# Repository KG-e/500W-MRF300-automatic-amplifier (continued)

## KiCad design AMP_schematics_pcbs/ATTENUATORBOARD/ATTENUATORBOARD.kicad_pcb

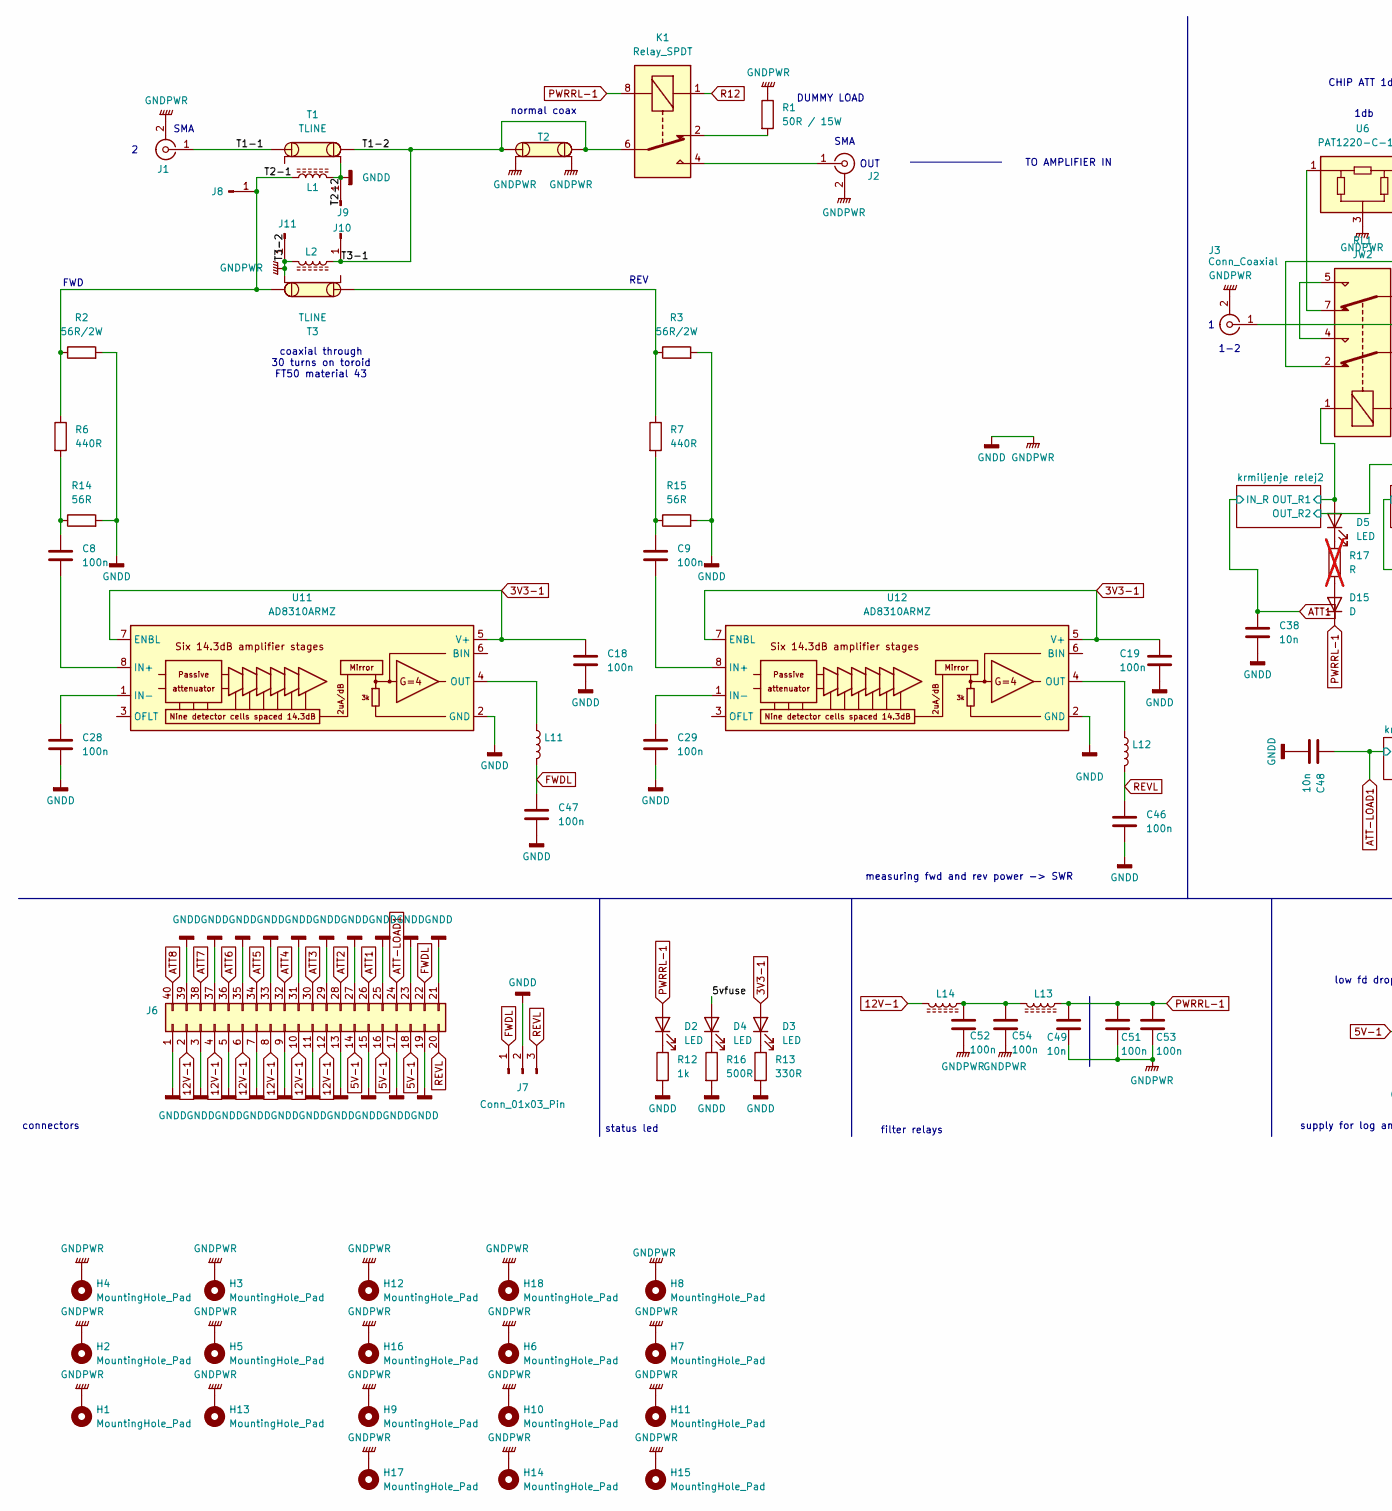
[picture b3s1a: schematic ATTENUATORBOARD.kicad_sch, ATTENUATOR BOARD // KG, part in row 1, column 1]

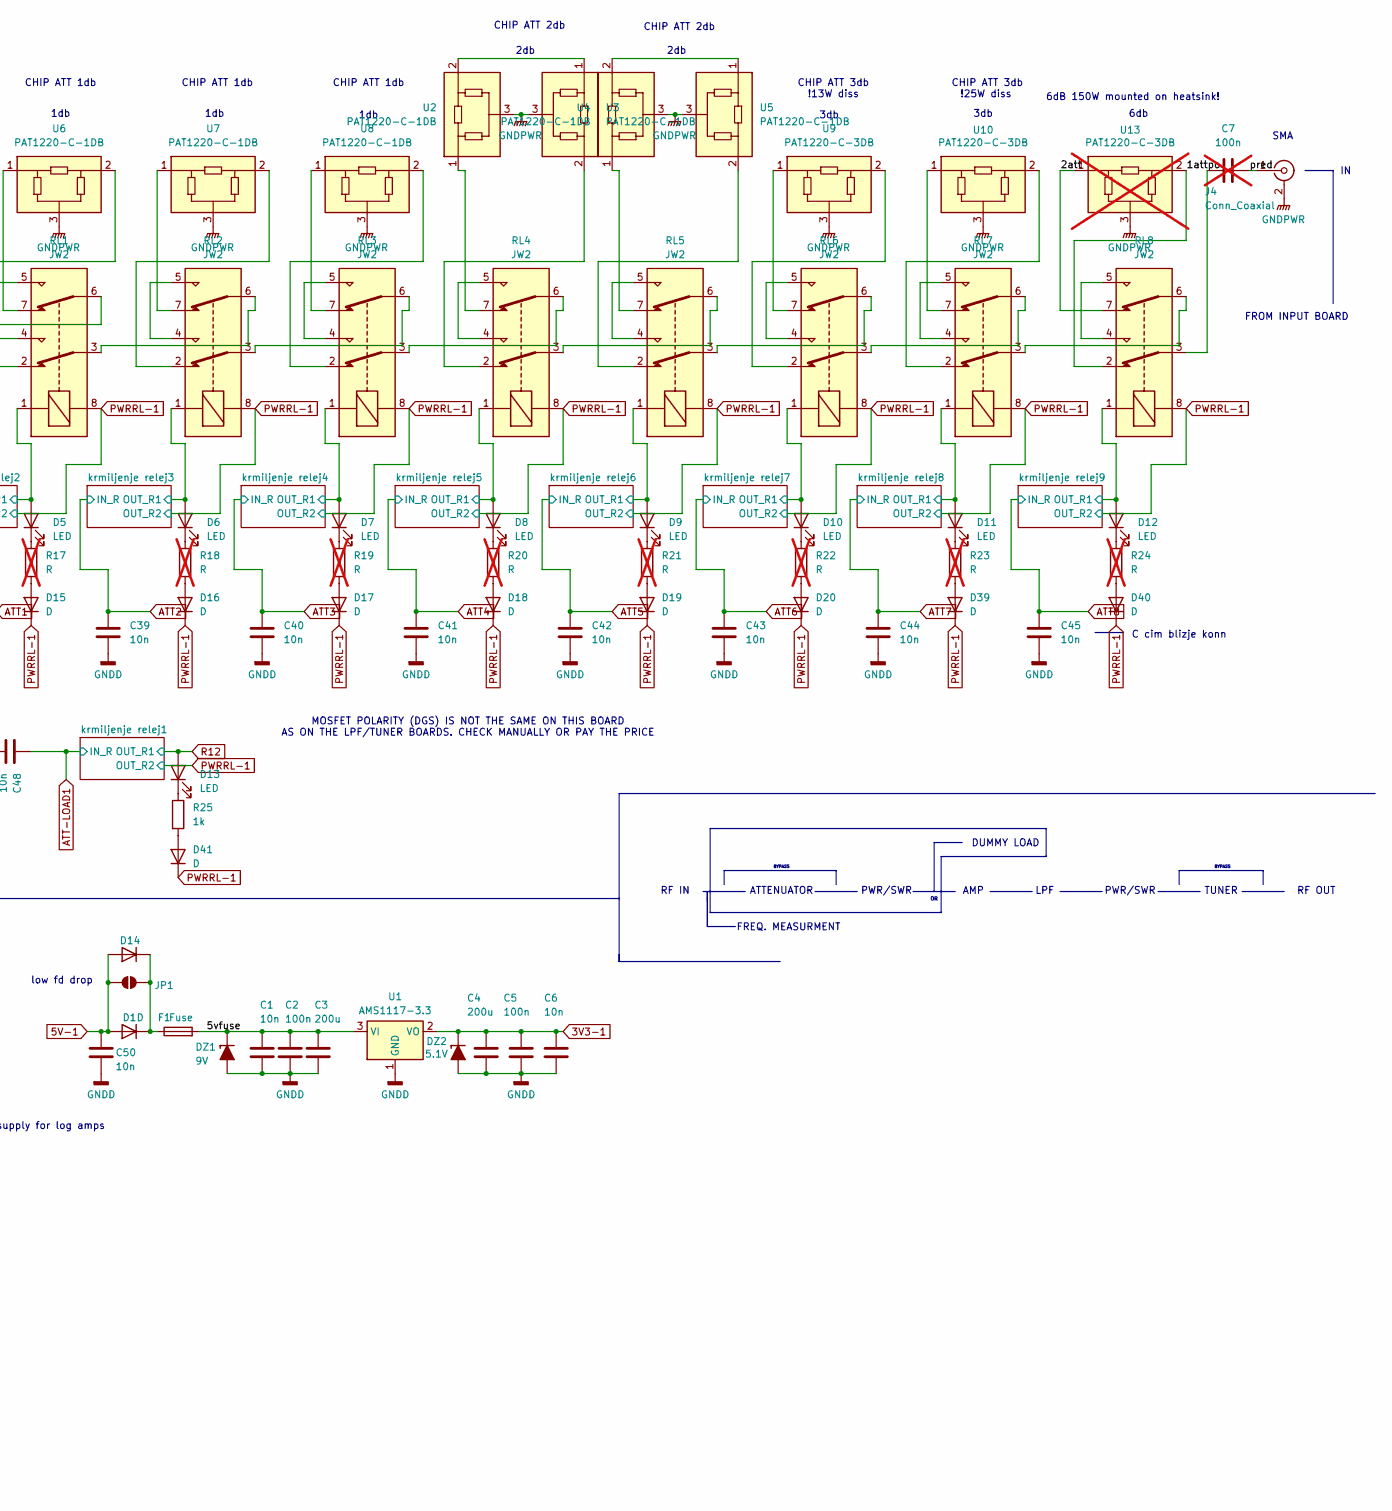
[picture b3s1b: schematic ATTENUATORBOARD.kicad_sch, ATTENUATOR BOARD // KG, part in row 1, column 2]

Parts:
C1, C6, C38, C39, C40, C41, C42, C43, C44, C45, C48, C49, C50: 10n; C_1206_3216Metric_Pad1.33x1.80mm_HandSolder
C2, C5, C8, C9, C18, C19, C28, C29, C46, C47, C51, C52, C53, C54: 100n; C_1206_3216Metric_Pad1.33x1.80mm_HandSolder
C3, C4: 200u; CP_Elec_8x10
C7: 100n; not fitted
D1: D; D_P600_R-6_P12.70mm_Horizontal
D2, D3, D4, D5, D6, D7, D8, D9, D10, D11, D12, D13: LED; LED_0805_2012Metric_Pad1.15x1.40mm_HandSolder
D14, D15, D16, D17, D18, D19, D20, D39, D40, D41: D; D_1206_3216Metric_Pad1.42x1.75mm_HandSolder
DZ1: 9V; D_SOD-123_Zener
DZ2: 5.1V; D_SOD-123_Zener
F1: Fuse; Fuse_1206_3216Metric
H1, H2, H3, H4, H5, H13: MountingHole_Pad; MountingHole_4.3mm_M4_Pad_TopBottom
H6, H7, H8, H9, H10, H11, H12, H14, H15, H16, H17, H18: MountingHole_Pad; MountingHole_3.2mm_M3_Pad_TopBottom
J1, J2, J3, J4: Conn_Coaxial; SMA_Amphenol_132134_Vertical
J6: Conn_02x20_Counter_Clockwise; PinHeader_2x20_P2.54mm_Vertical
J7: Conn_01x03_Pin; PinHeader_1x03_P2.54mm_Vertical
J8, J9, J10, J11: Conn_01x01_Pin; PinSocket_1x01_P2.54mm_Vertical
JP1: SolderJumper_2_Open; SolderJumper-2_P1.3mm_Open_Pad1.0x1.5mm
K1: Relay_SPDT; Relay_SPDT_Panasonic_JW1_FormC
L1, L2: L_Ferrite
L11, L12: L; Ferrite_1206_3216Metric_Pad1.42x1.75mm_BigPads
L13, L14: L_Ferrite; Ferrite_1206_3216Metric_Pad1.22x1.90mm_BigPads
R1: 50R / 15W; TO-220-2_Horizontal_TabDown
R2, R3: 56R/2W; R_2512_6332Metric_Pad1.40x3.35mm_HandSolder
R6, R7: 440R; R_1206_3216Metric_Pad1.30x1.75mm_HandSolder
R12, R25: 1k; R_1206_3216Metric_Pad1.30x1.75mm_HandSolder
R13: 330R; R_1206_3216Metric_Pad1.30x1.75mm_HandSolder
R14, R15: 56R; R_1206_3216Metric_Pad1.30x1.75mm_HandSolder
R16: 500R; R_1206_3216Metric_Pad1.30x1.75mm_HandSolder
R17, R18, R19, R20, R21, R22, R23, R24: R; R_1206_3216Metric_Pad1.30x1.75mm_HandSolder; not fitted
RL1, RL2, RL3, RL4, RL5, RL6, RL7, RL8: JW2; Relay_DPDT_Panasonic_JW2
T1, T2, T3: TLINE
U1: AMS1117-3.3; SOT-223-3_TabPin2
U2, U3, U4, U5, U6, U7, U8: PAT1220-C-1DB; ATT-CHIP
U9, U10: PAT1220-C-3DB; ATT-CHIP
U11, U12: AD8310ARMZ; MSOP-8_3x3mm_P0.65mm
U13: PAT1220-C-3DB; ATT-CHIP; not fitted

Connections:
3V3-1: C4.1, C5.1, C6.1, C18.1, C19.1, D3.2 (A), DZ2.1 (K), U1.2 (VO), U11.5 (V+), U11.7 (ENBL), U12.5 (V+), U12.7 (ENBL)
5V-1: C50.1, D1.2 (A), D14.2 (A), J6.14, J6.16, J6.18, JP1.1 (A)
12V-1: J6.2, J6.4, J6.6, J6.8, J6.10, J6.12, L14.2
/1att: RL8.2, U13.2
/2att: RL8.7, U13.1
/5vfuse: C1.1, C2.1, C3.1, D4.2 (A), DZ1.1 (K), F1.2, U1.3 (VI)
/T1-1: J1.1 (In), T1.1
/T1-2: J10.1, K1.6, L2.1, T1.3, T2.1, T2.3
/T2-1: J8.1, L1.1, R2.1, R6.1, T3.3
/krmiljenje relej2/OUT_R1: D5.2 (A), RL1.1; also elsewhere on the board
/krmiljenje relej3/OUT_R1: D6.2 (A), RL2.1; also elsewhere on the board
/krmiljenje relej4/OUT_R1: D7.2 (A), RL3.1; also elsewhere on the board
/krmiljenje relej5/OUT_R1: D8.2 (A), RL4.1; also elsewhere on the board
/krmiljenje relej6/OUT_R1: D9.2 (A), RL5.1; also elsewhere on the board
/krmiljenje relej7/OUT_R1: D10.2 (A), RL6.1; also elsewhere on the board
/krmiljenje relej8/OUT_R1: D11.2 (A), RL7.1; also elsewhere on the board
/krmiljenje relej9/OUT_R1: D12.2 (A), RL8.1; also elsewhere on the board
/po: C7.1, RL8.3
/pred: C7.2, J4.1 (In)
ATT1: C38.1, J6.26; also elsewhere on the board
ATT2: C39.1, J6.28; also elsewhere on the board
ATT3: C40.1, J6.30; also elsewhere on the board
ATT4: C41.1, J6.32; also elsewhere on the board
ATT5: C42.1, J6.34; also elsewhere on the board
ATT6: C43.1, J6.36; also elsewhere on the board
ATT7: C44.1, J6.38; also elsewhere on the board
ATT8: C45.1, J6.40; also elsewhere on the board
ATT-LOAD1: C48.1, J6.24; also elsewhere on the board
FWDL: C47.1, J6.22, J7.1, L11.2
GNDD: C1.2, C2.2, C3.2, C4.2, C5.2, C6.2, C18.2, C19.2, C28.2, C29.2, C38.2, C39.2, C40.2, C41.2, C42.2, C43.2, C44.2, C45.2, C46.2, C47.2, C48.2, C49.2, C50.2, C51.2, C52.2, C53.2, C54.2, DZ1.2 (A), DZ2.2 (A), H1.1, H2.1, H3.1, H4.1, H5.1, H6.1, H7.1, H8.1, H9.1, H10.1, H11.1, H12.1, H13.1, H14.1, H15.1, H16.1, H17.1, H18.1, J1.2 (Ext), J2.2 (Ext), J3.2 (Ext), J4.2 (Ext), J6.1, J6.3, J6.5, J6.7, J6.9, J6.11, J6.13, J6.15, J6.17, J6.19, J6.21, J6.23, J6.25, J6.27, J6.29, J6.31, J6.33, J6.35, J6.37, J6.39, J7.2, J9.1, J11.1, L1.2, L2.2, R1.1, R2.2, R3.2, R12.2, R13.2, R14.2, R15.2, R16.2, T1.4, T2.2, T2.4, T3.4, U1.1 (GND), U2.3, U3.3, U4.3, U5.3, U6.3, U7.3, U8.3, U9.3, U10.3, U11.2 (GND), U12.2 (GND), U13.3; also elsewhere on the board
unnamed: C8.1, R6.2, R14.1
unnamed: C9.1, R7.2, R15.1
unnamed: C52.1, C54.1, L13.2, L14.1
unnamed: D1.1 (K), D14.1 (K), F1.1, JP1.2 (B)
unnamed: D2.1 (K), R12.1
unnamed: D3.1 (K), R13.1
unnamed: D4.1 (K), R16.1
unnamed: D5.1 (K), R17.1
unnamed: D6.1 (K), R18.1
unnamed: D7.1 (K), R19.1
unnamed: D8.1 (K), R20.1
unnamed: D9.1 (K), R21.1
unnamed: D10.1 (K), R22.1
unnamed: D11.1 (K), R23.1
unnamed: D12.1 (K), R24.1
unnamed: D13.1 (K), R25.1
unnamed: D15.2 (A), R17.2
unnamed: D16.2 (A), R18.2
unnamed: D17.2 (A), R19.2
unnamed: D18.2 (A), R20.2
unnamed: D19.2 (A), R21.2
unnamed: D20.2 (A), R22.2
unnamed: D39.2 (A), R23.2
unnamed: D40.2 (A), R24.2
unnamed: D41.2 (A), R25.2
unnamed: J2.1 (In), K1.4
unnamed: J3.1 (In), RL1.6
unnamed: K1.2, R1.2
unnamed: R3.1, R7.1, T3.1
unnamed: RL1.2, U6.2
unnamed: RL1.3, RL2.6
unnamed: RL1.4, RL1.5
unnamed: RL1.7, U6.1
unnamed: RL2.2, U7.2
unnamed: RL2.3, RL3.6
unnamed: RL2.4, RL2.5
unnamed: RL2.7, U7.1
unnamed: RL3.2, U8.2
unnamed: RL3.3, RL4.6
unnamed: RL3.4, RL3.5
unnamed: RL3.7, U8.1
unnamed: RL4.2, U3.2
unnamed: RL4.3, RL5.6
unnamed: RL4.4, RL4.5
unnamed: RL4.7, U2.1
unnamed: RL5.2, U5.2
unnamed: RL5.3, RL6.6
unnamed: RL5.4, RL5.5
unnamed: RL5.7, U4.1
unnamed: RL6.2, U9.2
unnamed: RL6.3, RL7.6
unnamed: RL6.4, RL6.5
unnamed: RL6.7, U9.1
unnamed: RL7.2, U10.2
unnamed: RL7.3, RL8.6
unnamed: RL7.4, RL7.5
unnamed: RL7.7, U10.1
unnamed: RL8.4, RL8.5
unnamed: U2.2, U3.1
unnamed: U4.2, U5.1
unnamed: C8.2, U11.8 (IN+)
unnamed: C28.1, U11.1 (IN-)
unnamed: L11.1, U11.4 (OUT)
unnamed: C9.2, U12.8 (IN+)
unnamed: C29.1, U12.1 (IN-)
unnamed: L12.1, U12.4 (OUT)
PWRRL-1: C49.1, C51.1, C53.1, D2.2 (A), D15.1 (K), D16.1 (K), D17.1 (K), D18.1 (K), D19.1 (K), D20.1 (K), D39.1 (K), D40.1 (K), D41.1 (K), K1.8, L13.1, RL1.8, RL2.8, RL3.8, RL4.8, RL5.8, RL6.8, RL7.8, RL8.8; also elsewhere on the board
R12: D13.2 (A), K1.1; also elsewhere on the board
REVL: C46.1, J6.20, J7.3, L12.2

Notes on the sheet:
RF OUT
TO AMPLIFIER IN
RF IN
CHIP ATT 3db
CHIP ATT 1db
3db
FREQ. MEASURMENT
coaxial through 30 turns on toroid FT50 material 43
!13W diss
1-2
6db
BYPASS
ATTENUATOR
SMA
AMP
CHIP ATT 2db
filter relays
1db
REV
measuring fwd and rev power -> SWR
connectors
PWR/SWR
6dB 150W mounted on heatsink!
normal coax
status led
TUNER
DUMMY LOAD
LPF
FROM INPUT BOARD
OUT
!25W diss
FWD
low fd drop
2db
C cim blizje konn
supply for log amps
MOSFET POLARITY (DGS) IS NOT THE SAME ON THIS BOARD AS ON THE LPF/TUNER BOARDS. CHECK MANUALLY OR PAY THE PRICE

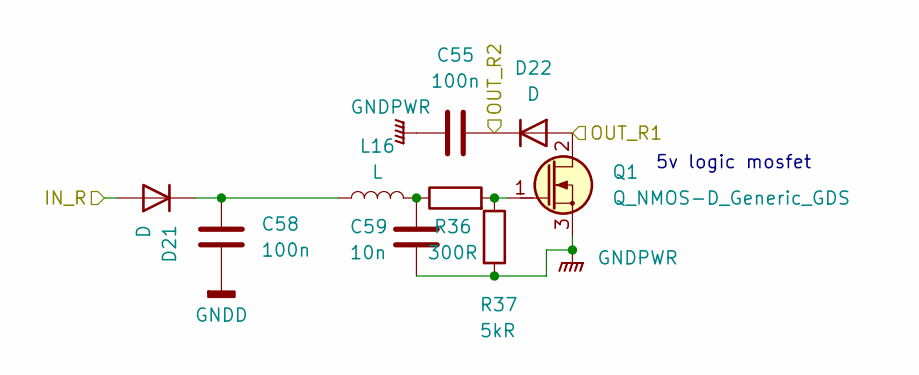
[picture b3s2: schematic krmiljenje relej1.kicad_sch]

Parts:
C55, C58: 100n; C_1206_3216Metric_Pad1.33x1.80mm_HandSolder
C59: 10n; C_1206_3216Metric_Pad1.33x1.80mm_HandSolder
D21, D22: D; D_1206_3216Metric_Pad1.42x1.75mm_HandSolder
L16: L; Ferrite_1206_3216Metric_Pad1.42x1.75mm_BigPads
Q1: Q_NMOS-D_Generic_GDS; TSOT-23_HandSoldering
R36: 300R; R_1206_3216Metric_Pad1.30x1.75mm_HandSolder
R37: 5kR; R_1206_3216Metric_Pad1.30x1.75mm_HandSolder

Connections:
ATT-LOAD1: D21.2 (A); also elsewhere on the board
GNDD: C55.2, C58.2, C59.2, Q1.3 (S), R37.2; also elsewhere on the board
unnamed: C59.1, L16.2, R36.1
unnamed: C58.1, D21.1 (K), L16.1
unnamed: Q1.1 (G), R36.2, R37.1
PWRRL-1: C55.1, D22.1 (K); also elsewhere on the board
R12: D22.2 (A), Q1.2 (D); also elsewhere on the board

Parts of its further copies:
C56, C57, C60, C62, C64, C66, C67, C69, C70, C72, C73, C75, C76, C78, C79, C81: 100n; C_1206_3216Metric_Pad1.33x1.80mm_HandSolder
C61, C63, C65, C68, C71, C74, C77, C80: 10n; C_1206_3216Metric_Pad1.33x1.80mm_HandSolder
D23, D24, D25, D26, D27, D28, D29, D30, D31, D32, D33, D34, D35, D36, D37, D38: D; D_1206_3216Metric_Pad1.42x1.75mm_HandSolder
L17, L18, L19, L20, L21, L22, L23, L24: L; Ferrite_1206_3216Metric_Pad1.42x1.75mm_BigPads
Q2, Q3, Q4, Q5, Q6, Q7, Q8, Q9: Q_NMOS-D_Generic_GDS; TSOT-23_HandSoldering
R38, R40, R42, R44, R46, R48, R50, R52: 300R; R_1206_3216Metric_Pad1.30x1.75mm_HandSolder
R39, R41, R43, R45, R47, R49, R51, R53: 5kR; R_1206_3216Metric_Pad1.30x1.75mm_HandSolder

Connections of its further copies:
/krmiljenje relej2/OUT_R1: D24.2 (A), Q2.2 (D); also elsewhere on the board
/krmiljenje relej3/OUT_R1: D26.2 (A), Q3.2 (D); also elsewhere on the board
/krmiljenje relej4/OUT_R1: D28.2 (A), Q4.2 (D); also elsewhere on the board
/krmiljenje relej5/OUT_R1: D30.2 (A), Q5.2 (D); also elsewhere on the board
/krmiljenje relej6/OUT_R1: D32.2 (A), Q6.2 (D); also elsewhere on the board
/krmiljenje relej7/OUT_R1: D34.2 (A), Q7.2 (D); also elsewhere on the board
/krmiljenje relej8/OUT_R1: D36.2 (A), Q8.2 (D); also elsewhere on the board
/krmiljenje relej9/OUT_R1: D38.2 (A), Q9.2 (D); also elsewhere on the board
ATT1: D23.2 (A); also elsewhere on the board
ATT2: D25.2 (A); also elsewhere on the board
ATT3: D27.2 (A); also elsewhere on the board
ATT4: D29.2 (A); also elsewhere on the board
ATT5: D31.2 (A); also elsewhere on the board
ATT6: D33.2 (A); also elsewhere on the board
ATT7: D35.2 (A); also elsewhere on the board
ATT8: D37.2 (A); also elsewhere on the board
GNDD: C56.2, C57.2, C60.2, C61.2, C62.2, C63.2, C64.2, C65.2, C66.2, C67.2, C68.2, C69.2, C70.2, C71.2, C72.2, C73.2, C74.2, C75.2, C76.2, C77.2, C78.2, C79.2, C80.2, C81.2, Q2.3 (S), Q3.3 (S), Q4.3 (S), Q5.3 (S), Q6.3 (S), Q7.3 (S), Q8.3 (S), Q9.3 (S), R39.2, R41.2, R43.2, R45.2, R47.2, R49.2, R51.2, R53.2; also elsewhere on the board
unnamed: C61.1, L17.2, R38.1
unnamed: C63.1, L18.2, R40.1
unnamed: C65.1, L19.2, R42.1
unnamed: C68.1, L20.2, R44.1
unnamed: C71.1, L21.2, R46.1
unnamed: C74.1, L22.2, R48.1
unnamed: C77.1, L23.2, R50.1
unnamed: C80.1, L24.2, R52.1
unnamed: C60.1, D23.1 (K), L17.1
unnamed: C62.1, D25.1 (K), L18.1
unnamed: C64.1, D27.1 (K), L19.1
unnamed: C67.1, D29.1 (K), L20.1
unnamed: C70.1, D31.1 (K), L21.1
unnamed: C73.1, D33.1 (K), L22.1
unnamed: C76.1, D35.1 (K), L23.1
unnamed: C79.1, D37.1 (K), L24.1
unnamed: Q2.1 (G), R38.2, R39.1
unnamed: Q3.1 (G), R40.2, R41.1
unnamed: Q4.1 (G), R42.2, R43.1
unnamed: Q5.1 (G), R44.2, R45.1
unnamed: Q6.1 (G), R46.2, R47.1
unnamed: Q7.1 (G), R48.2, R49.1
unnamed: Q8.1 (G), R50.2, R51.1
unnamed: Q9.1 (G), R52.2, R53.1
PWRRL-1: C56.1, C57.1, C66.1, C69.1, C72.1, C75.1, C78.1, C81.1, D24.1 (K), D26.1 (K), D28.1 (K), D30.1 (K), D32.1 (K), D34.1 (K), D36.1 (K), D38.1 (K); also elsewhere on the board

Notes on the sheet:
5v logic mosfet

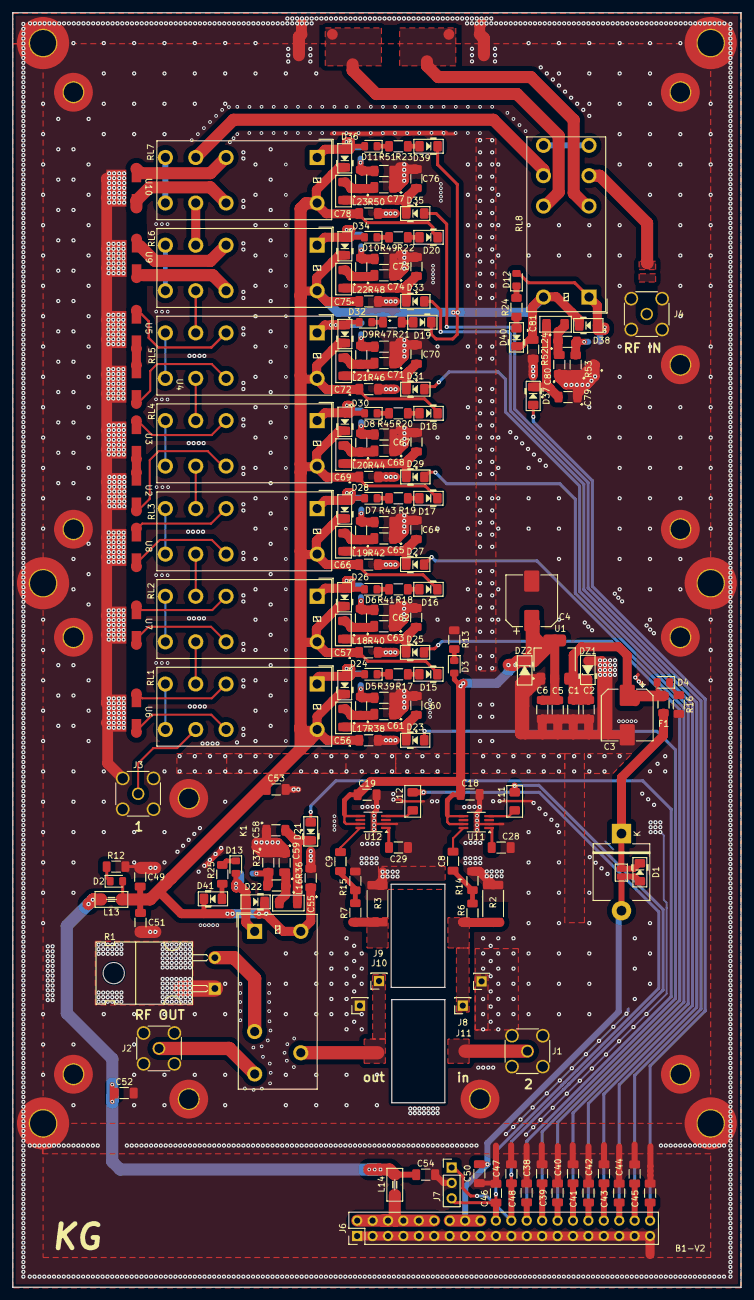
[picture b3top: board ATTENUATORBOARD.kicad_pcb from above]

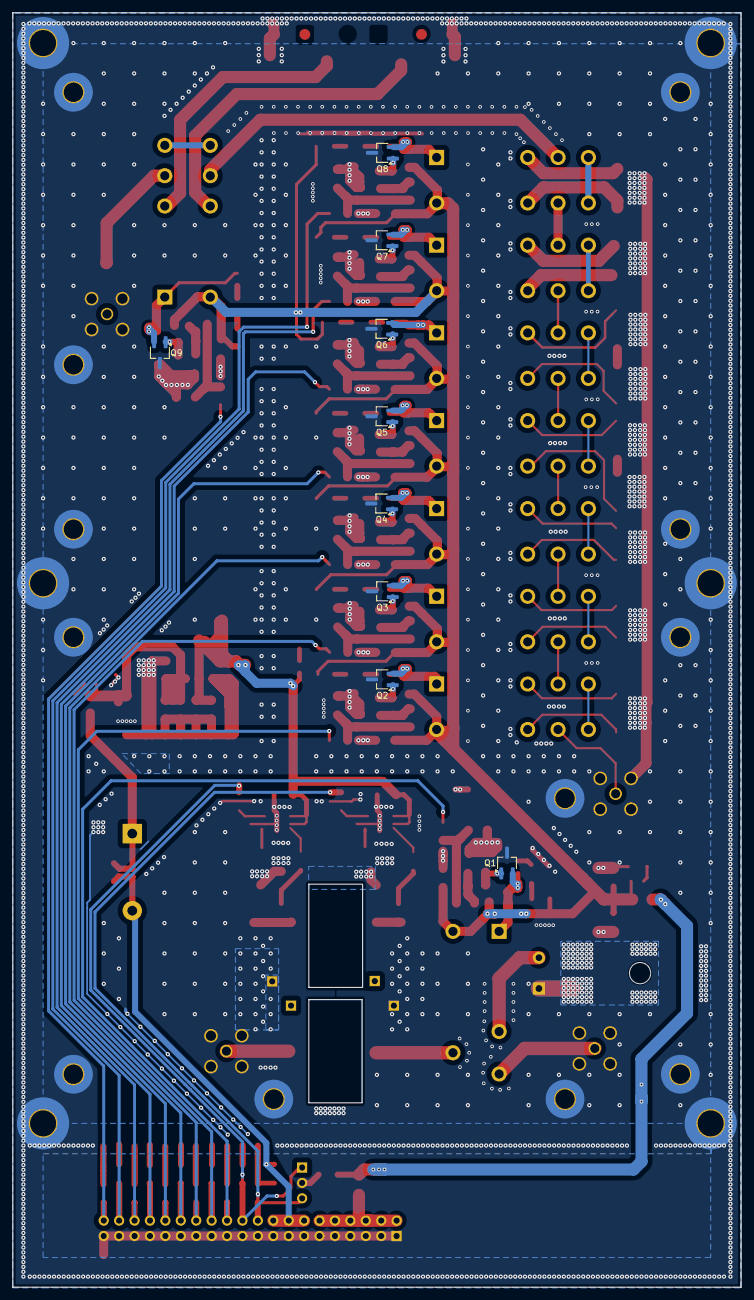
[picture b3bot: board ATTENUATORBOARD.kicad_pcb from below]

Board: 4 copper layers, 120.0 x 210.0 mm, 209 parts (9 on the bottom side), 121 nets.

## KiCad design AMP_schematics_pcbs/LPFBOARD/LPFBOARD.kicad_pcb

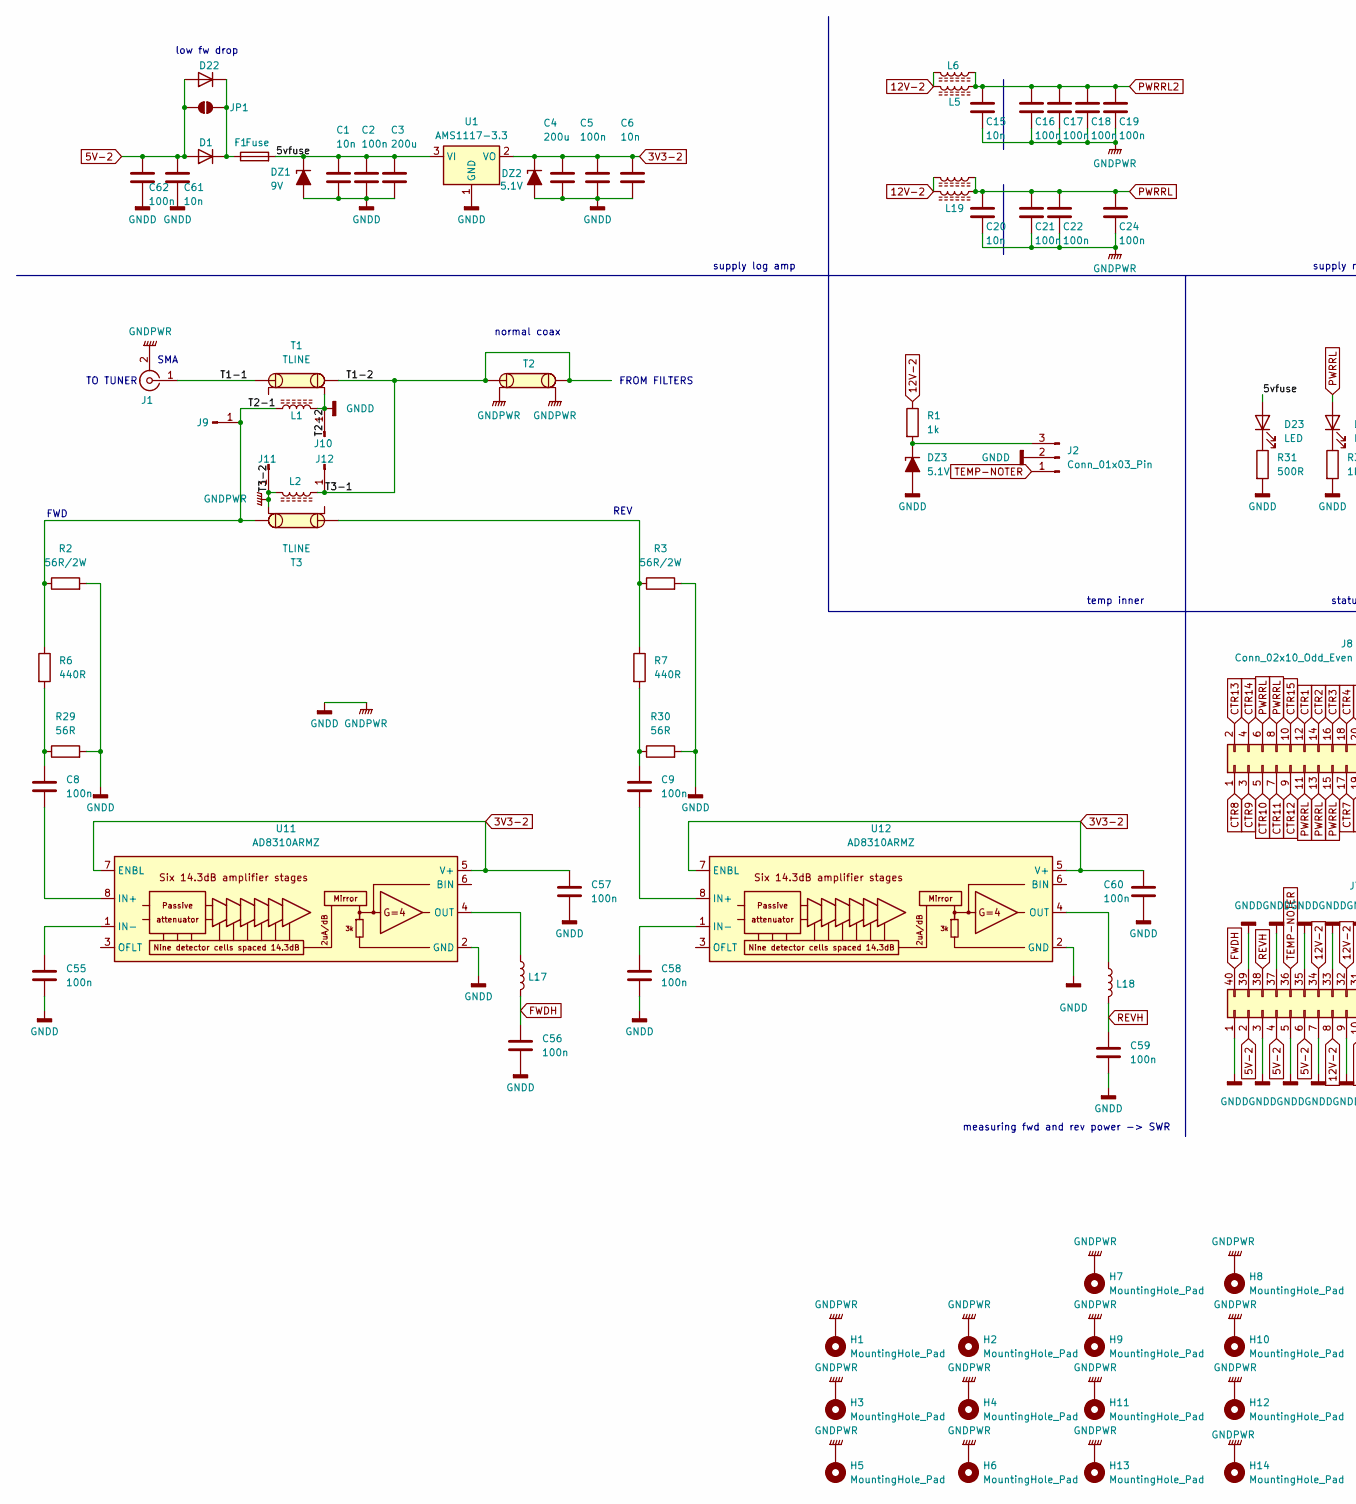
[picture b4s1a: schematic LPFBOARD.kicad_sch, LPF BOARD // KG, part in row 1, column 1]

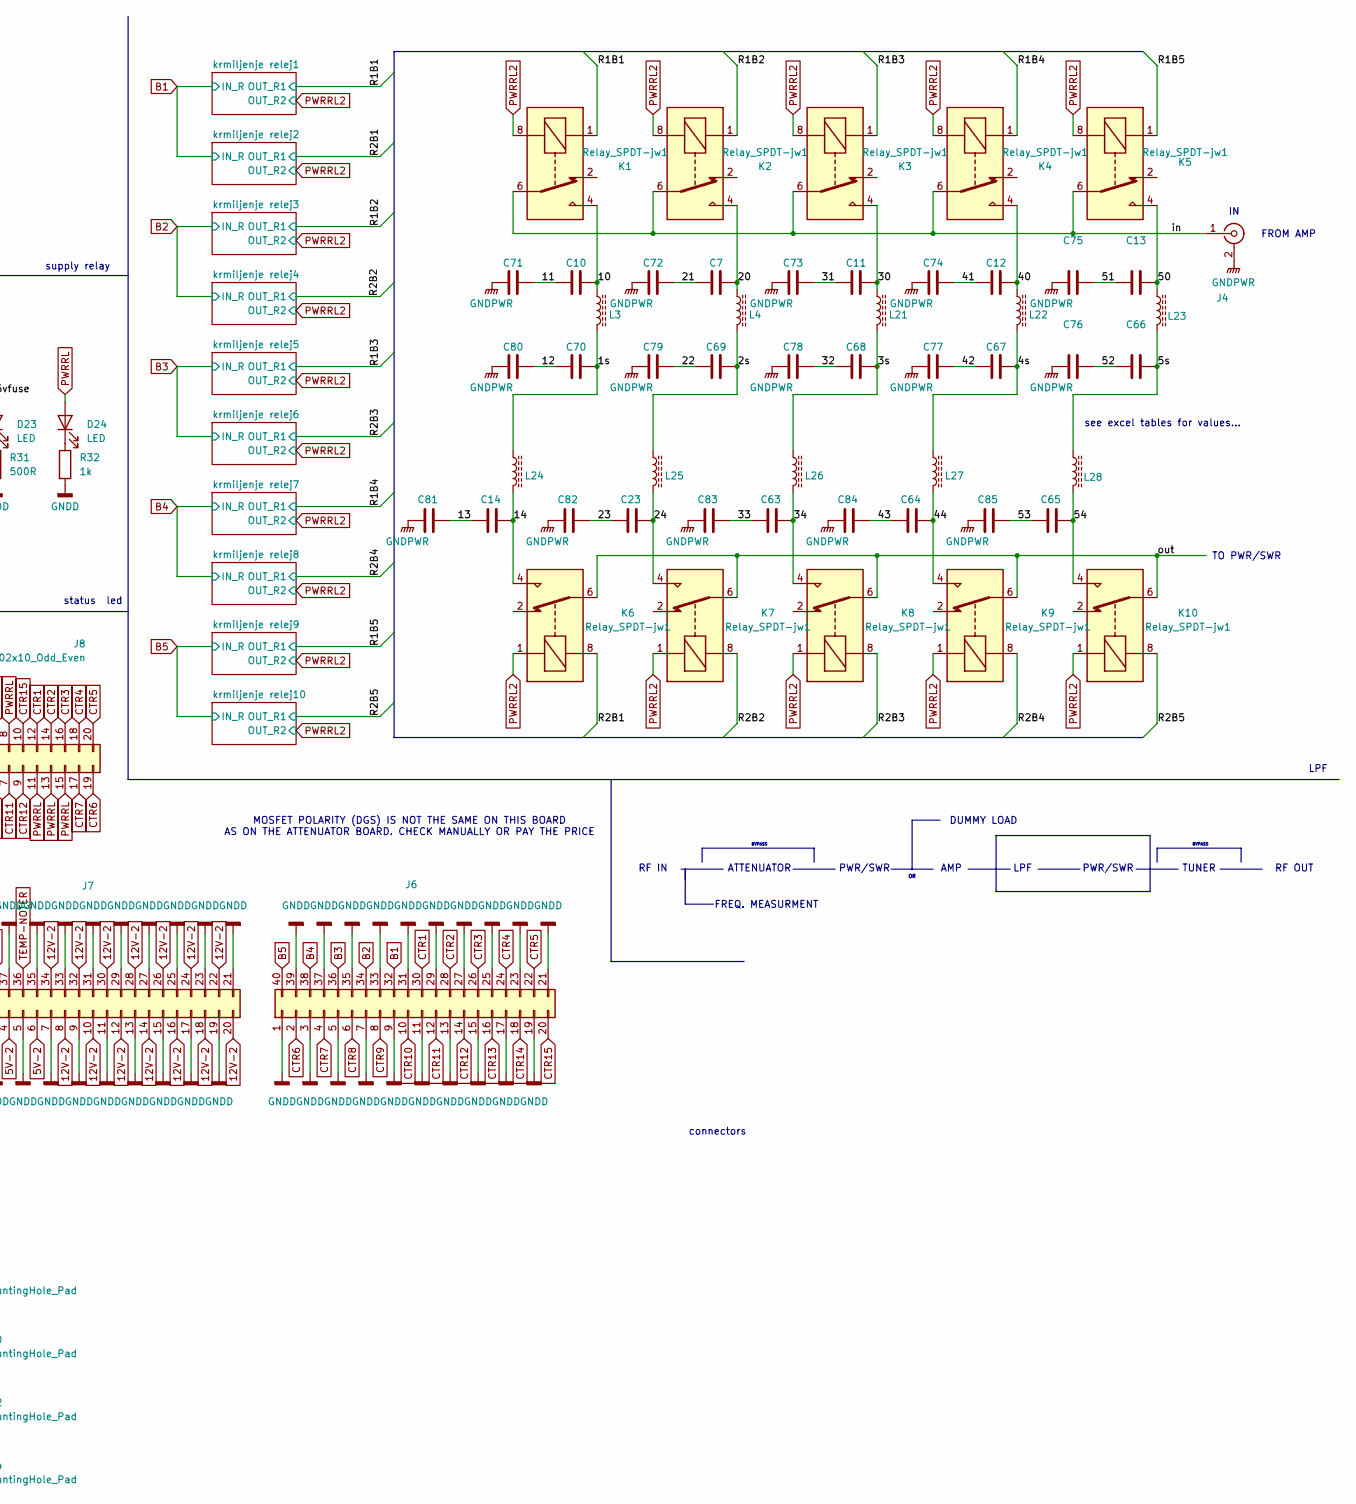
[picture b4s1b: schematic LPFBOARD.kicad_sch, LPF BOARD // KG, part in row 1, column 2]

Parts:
C1, C6, C15, C20, C61: 10n; C_1206_3216Metric_Pad1.33x1.80mm_HandSolder
C2, C5, C8, C9, C16, C17, C18, C19, C21, C22, C24, C55, C56, C57, C58, C59, C60, C62: 100n; C_1206_3216Metric_Pad1.33x1.80mm_HandSolder
C3, C4: 200u; CP_Elec_8x10
C7, C10, C11, C12, C13, C14, C23, C63, C64, C65, C66, C67, C68, C69, C70, C71, C72, C73, C74, C75, C76, C77, C78, C79, C80, C81, C82, C83, C84, C85: C; C_2220_5750Metric_Pad1.97x5.40mm_HandSolder
D1: D; D_P600_R-6_P12.70mm_Horizontal
D22: D; D_1206_3216Metric_Pad1.42x1.75mm_HandSolder
D23, D24: LED; LED_0805_2012Metric_Pad1.15x1.40mm_HandSolder
DZ1: 9V; D_SOD-123_Zener
DZ2: 5.1V; D_SOD-123_Zener
DZ3: 5.1V; D_A-405_P7.62mm_Horizontal
F1: Fuse; Fuse_1206_3216Metric
H1, H2, H3, H4, H5, H6: MountingHole_Pad; MountingHole_4.3mm_M4_Pad_TopBottom
H7, H8, H9, H10, H11, H12, H13, H14: MountingHole_Pad; MountingHole_3.2mm_M3_Pad_TopBottom
J1, J4: Conn_Coaxial; SMA_Amphenol_132134_Vertical
J2: Conn_01x03_Pin; PinSocket_1x03_P2.54mm_Vertical
J6, J7: Conn_02x20_Counter_Clockwise; PinHeader_2x20_P2.54mm_Vertical
J8: Conn_02x10_Odd_Even; PinHeader_2x10_P2.54mm_Vertical
J9, J10, J11, J12: Conn_01x01_Pin; PinSocket_1x01_P2.54mm_Vertical
JP1: SolderJumper_2_Open; SolderJumper-2_P1.3mm_Open_Pad1.0x1.5mm
K1, K2, K3, K4, K5, K6, K7, K8, K9, K10: Relay_SPDT-jw1; Relay_SPDT_Panasonic_JW1_FormC
L1, L2: L_Ferrite
L3, L4, L21, L22, L23, L24, L25, L26, L27, L28: L_Ferrite; T80_footprint
L5, L6, L19, L20: L_Ferrite; Ferrite_1206_3216Metric_Pad1.42x1.75mm_BigPads
L17, L18: L; Ferrite_1206_3216Metric_Pad1.42x1.75mm_BigPads
R1, R32: 1k; R_1206_3216Metric_Pad1.30x1.75mm_HandSolder
R2, R3: 56R/2W; R_2512_6332Metric_Pad1.40x3.35mm_HandSolder
R6, R7: 440R; R_1206_3216Metric_Pad1.30x1.75mm_HandSolder
R29, R30: 56R; R_1206_3216Metric_Pad1.30x1.75mm_HandSolder
R31: 500R; R_1206_3216Metric_Pad1.30x1.75mm_HandSolder
T1, T2, T3: TLINE
U1: AMS1117-3.3; SOT-223-3_TabPin2
U11, U12: AD8310ARMZ; MSOP-8_3x3mm_P0.65mm

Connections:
3V3-2: C4.1, C5.1, C6.1, C57.1, C60.1, DZ2.1 (K), U1.2 (VO), U11.5 (V+), U11.7 (ENBL), U12.5 (V+), U12.7 (ENBL)
5V-2: C61.1, C62.1, D1.2 (A), D22.2 (A), J7.2, J7.4, J7.6, JP1.1 (A)
12V-2: J7.8, J7.10, J7.12, J7.14, J7.16, J7.18, J7.20, J7.22, J7.24, J7.26, J7.28, J7.30, J7.32, J7.34, L5.2, L6.2, L19.2, L20.2, R1.1
/1s: C70.2, L3.2, L24.1
/2s: C69.2, L4.2, L25.1
/3s: C68.2, L21.2, L26.1
/4s: C67.2, L22.2, L27.1
/5s: C66.1, L23.2, L28.1
/5vfuse: C1.1, C2.1, C3.1, D23.2 (A), DZ1.1 (K), F1.2, U1.3 (VI)
/10: C10.2, K1.4, L3.1
/11: C10.1, C71.2
/12: C70.1, C80.2
/13: C14.1, C81.2
/14: C14.2, K6.4, L24.2
/20: C7.2, K2.4, L4.1
/21: C7.1, C72.2
/22: C69.1, C79.2
/23: C23.1, C82.2
/24: C23.2, K7.4, L25.2
/30: C11.2, K3.4, L21.1
/31: C11.1, C73.2
/32: C68.1, C78.2
/33: C63.1, C83.2
/34: C63.2, K8.4, L26.2
/40: C12.2, K4.4, L22.1
/41: C12.1, C74.2
/42: C67.1, C77.2
/43: C64.1, C84.2
/44: C64.2, K9.4, L27.2
/50: C13.2, K5.4, L23.1
/51: C13.1, C75.2
/52: C66.2, C76.2
/53: C65.1, C85.2
/54: C65.2, K10.4, L28.2
/R1B1: K1.1; also elsewhere on the board
/R1B2: K2.1; also elsewhere on the board
/R1B3: K3.1; also elsewhere on the board
/R1B4: K4.1; also elsewhere on the board
/R1B5: K5.1; also elsewhere on the board
/R2B1: K6.8; also elsewhere on the board
/R2B2: K7.8; also elsewhere on the board
/R2B3: K8.8; also elsewhere on the board
/R2B4: K9.8; also elsewhere on the board
/R2B5: K10.8; also elsewhere on the board
/T1-1: J1.1 (In), T1.1
/T1-2: J12.1, L2.1, T1.3, T2.1, T2.3
/T2-1: J9.1, L1.1, R2.1, R6.1, T3.3
/in: J4.1 (In), K1.6, K2.6, K3.6, K4.6, K5.6
/out: K6.6, K7.6, K8.6, K9.6, K10.6
B1: J6.32; also elsewhere on the board
B2: J6.34; also elsewhere on the board
B3: J6.36; also elsewhere on the board
B4: J6.38; also elsewhere on the board
B5: J6.40; also elsewhere on the board
CTR1: J6.30, J8.12
CTR2: J6.28, J8.14
CTR3: J6.26, J8.16
CTR4: J6.24, J8.18
CTR5: J6.22, J8.20
CTR6: J6.2, J8.19
CTR7: J6.4, J8.17
CTR8: J6.6, J8.1
CTR9: J6.8, J8.3
CTR10: J6.10, J8.5
CTR11: J6.12, J8.7
CTR12: J6.14, J8.9
CTR13: J6.16, J8.2
CTR14: J6.18, J8.4
CTR15: J6.20, J8.10
FWDH: C56.1, J7.40, L17.2
GNDD: C1.2, C2.2, C3.2, C4.2, C5.2, C6.2, C15.2, C16.2, C17.2, C18.2, C19.2, C20.2, C21.2, C22.2, C24.2, C55.2, C56.2, C57.2, C58.2, C59.2, C60.2, C61.2, C62.2, C71.1, C72.1, C73.1, C74.1, C75.1, C76.1, C77.1, C78.1, C79.1, C80.1, C81.1, C82.1, C83.1, C84.1, C85.1, DZ1.2 (A), DZ2.2 (A), DZ3.2 (A), H1.1, H2.1, H3.1, H4.1, H5.1, H6.1, H7.1, H8.1, H9.1, H10.1, H11.1, H12.1, H13.1, H14.1, J1.2 (Ext), J2.2, J4.2 (Ext), J6.1, J6.3, J6.5, J6.7, J6.9, J6.11, J6.13, J6.15, J6.17, J6.19, J6.21, J6.23, J6.25, J6.27, J6.29, J6.31, J6.33, J6.35, J6.37, J6.39, J7.1, J7.3, J7.5, J7.7, J7.9, J7.11, J7.13, J7.15, J7.17, J7.19, J7.21, J7.23, J7.25, J7.27, J7.29, J7.31, J7.33, J7.35, J7.37, J7.39, J10.1, J11.1, L1.2, L2.2, R2.2, R3.2, R29.2, R30.2, R31.2, R32.2, T1.4, T2.2, T2.4, T3.4, U1.1 (GND), U11.2 (GND), U12.2 (GND); also elsewhere on the board
unnamed: C8.1, R6.2, R29.1
unnamed: C9.1, R7.2, R30.1
unnamed: D1.1 (K), D22.1 (K), F1.1, JP1.2 (B)
unnamed: D23.1 (K), R31.1
unnamed: D24.1 (K), R32.1
unnamed: DZ3.1 (K), J2.3, R1.2
unnamed: R3.1, R7.1, T3.1
unnamed: C8.2, U11.8 (IN+)
unnamed: C55.1, U11.1 (IN-)
unnamed: L17.1, U11.4 (OUT)
unnamed: C9.2, U12.8 (IN+)
unnamed: C58.1, U12.1 (IN-)
unnamed: L18.1, U12.4 (OUT)
PWRRL: C20.1, C21.1, C22.1, C24.1, D24.2 (A), J8.6, J8.8, J8.11, J8.13, J8.15, L19.1, L20.1
PWRRL2: C15.1, C16.1, C17.1, C18.1, C19.1, K1.8, K2.8, K3.8, K4.8, K5.8, K6.1, K7.1, K8.1, K9.1, K10.1, L5.1, L6.1; also elsewhere on the board
REVH: C59.1, J7.38, L18.2
TEMP-NOTER: J2.1, J7.36

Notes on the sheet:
BYPASS
DUMMY LOAD
temp inner
MOSFET POLARITY (DGS) IS NOT THE SAME ON THIS BOARD AS ON THE ATTENUATOR BOARD. CHECK MANUALLY OR PAY THE PRICE
FWD
ATTENUATOR
PWR/SWR
LPF
normal coax
RF IN
connectors
supply relay
FROM AMP
REV
FREQ. MEASURMENT
supply log amp
status led
AMP
FROM FILTERS
SMA
low fw drop
measuring fwd and rev power -> SWR
RF OUT
TUNER
see excel tables for values...
TO PWR/SWR
TO TUNER

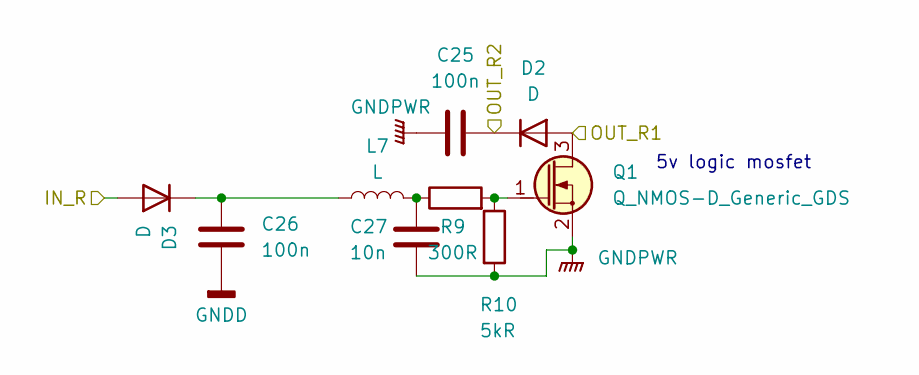
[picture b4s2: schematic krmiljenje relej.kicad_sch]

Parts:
C25, C26: 100n; C_1206_3216Metric_Pad1.33x1.80mm_HandSolder
C27: 10n; C_1206_3216Metric_Pad1.33x1.80mm_HandSolder
D2, D3: D; D_1206_3216Metric_Pad1.42x1.75mm_HandSolder
L7: L; Ferrite_1206_3216Metric_Pad1.42x1.75mm_BigPads
Q1: Q_NMOS-D_Generic_GDS; TSOT-23_HandSoldering
R9: 300R; R_1206_3216Metric_Pad1.30x1.75mm_HandSolder
R10: 5kR; R_1206_3216Metric_Pad1.30x1.75mm_HandSolder

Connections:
/R1B1: D2.2 (A), Q1.3 (D); also elsewhere on the board
B1: D3.2 (A); also elsewhere on the board
GNDD: C25.2, C26.2, C27.2, Q1.2 (S), R10.2; also elsewhere on the board
unnamed: C27.1, L7.2, R9.1
unnamed: C26.1, D3.1 (K), L7.1
unnamed: Q1.1 (G), R9.2, R10.1
PWRRL2: C25.1, D2.1 (K); also elsewhere on the board

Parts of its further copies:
C28, C29, C31, C32, C34, C35, C37, C38, C40, C41, C43, C44, C46, C47, C49, C50, C52, C53: 100n; C_1206_3216Metric_Pad1.33x1.80mm_HandSolder
C30, C33, C36, C39, C42, C45, C48, C51, C54: 10n; C_1206_3216Metric_Pad1.33x1.80mm_HandSolder
D4, D5, D6, D7, D8, D9, D10, D11, D12, D13, D14, D15, D16, D17, D18, D19, D20, D21: D; D_1206_3216Metric_Pad1.42x1.75mm_HandSolder
L8, L9, L10, L11, L12, L13, L14, L15, L16: L; Ferrite_1206_3216Metric_Pad1.42x1.75mm_BigPads
Q2, Q3, Q4, Q5, Q6, Q7, Q8, Q9, Q10: Q_NMOS-D_Generic_GDS; TSOT-23_HandSoldering
R11, R13, R15, R17, R19, R21, R23, R25, R27: 300R; R_1206_3216Metric_Pad1.30x1.75mm_HandSolder
R12, R14, R16, R18, R20, R22, R24, R26, R28: 5kR; R_1206_3216Metric_Pad1.30x1.75mm_HandSolder

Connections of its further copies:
/R1B2: D6.2 (A), Q3.3 (D); also elsewhere on the board
/R1B3: D10.2 (A), Q5.3 (D); also elsewhere on the board
/R1B4: D14.2 (A), Q7.3 (D); also elsewhere on the board
/R1B5: D18.2 (A), Q9.3 (D); also elsewhere on the board
/R2B1: D4.2 (A), Q2.3 (D); also elsewhere on the board
/R2B2: D8.2 (A), Q4.3 (D); also elsewhere on the board
/R2B3: D12.2 (A), Q6.3 (D); also elsewhere on the board
/R2B4: D16.2 (A), Q8.3 (D); also elsewhere on the board
/R2B5: D20.2 (A), Q10.3 (D); also elsewhere on the board
B1: D5.2 (A); also elsewhere on the board
B2: D7.2 (A), D9.2 (A); also elsewhere on the board
B3: D11.2 (A), D13.2 (A); also elsewhere on the board
B4: D15.2 (A), D17.2 (A); also elsewhere on the board
B5: D19.2 (A), D21.2 (A); also elsewhere on the board
GNDD: C28.2, C29.2, C30.2, C31.2, C32.2, C33.2, C34.2, C35.2, C36.2, C37.2, C38.2, C39.2, C40.2, C41.2, C42.2, C43.2, C44.2, C45.2, C46.2, C47.2, C48.2, C49.2, C50.2, C51.2, C52.2, C53.2, C54.2, Q2.2 (S), Q3.2 (S), Q4.2 (S), Q5.2 (S), Q6.2 (S), Q7.2 (S), Q8.2 (S), Q9.2 (S), Q10.2 (S), R12.2, R14.2, R16.2, R18.2, R20.2, R22.2, R24.2, R26.2, R28.2; also elsewhere on the board
unnamed: C30.1, L8.2, R11.1
unnamed: C33.1, L9.2, R13.1
unnamed: C36.1, L10.2, R15.1
unnamed: C39.1, L11.2, R17.1
unnamed: C42.1, L12.2, R19.1
unnamed: C45.1, L13.2, R21.1
unnamed: C48.1, L14.2, R23.1
unnamed: C51.1, L15.2, R25.1
unnamed: C54.1, L16.2, R27.1
unnamed: C29.1, D5.1 (K), L8.1
unnamed: C32.1, D7.1 (K), L9.1
unnamed: C35.1, D9.1 (K), L10.1
unnamed: C38.1, D11.1 (K), L11.1
unnamed: C41.1, D13.1 (K), L12.1
unnamed: C44.1, D15.1 (K), L13.1
unnamed: C47.1, D17.1 (K), L14.1
unnamed: C50.1, D19.1 (K), L15.1
unnamed: C53.1, D21.1 (K), L16.1
unnamed: Q2.1 (G), R11.2, R12.1
unnamed: Q3.1 (G), R13.2, R14.1
unnamed: Q4.1 (G), R15.2, R16.1
unnamed: Q5.1 (G), R17.2, R18.1
unnamed: Q6.1 (G), R19.2, R20.1
unnamed: Q7.1 (G), R21.2, R22.1
unnamed: Q8.1 (G), R23.2, R24.1
unnamed: Q9.1 (G), R25.2, R26.1
unnamed: Q10.1 (G), R27.2, R28.1
PWRRL2: C28.1, C31.1, C34.1, C37.1, C40.1, C43.1, C46.1, C49.1, C52.1, D4.1 (K), D6.1 (K), D8.1 (K), D10.1 (K), D12.1 (K), D14.1 (K), D16.1 (K), D18.1 (K), D20.1 (K); also elsewhere on the board

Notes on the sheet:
5v logic mosfet
